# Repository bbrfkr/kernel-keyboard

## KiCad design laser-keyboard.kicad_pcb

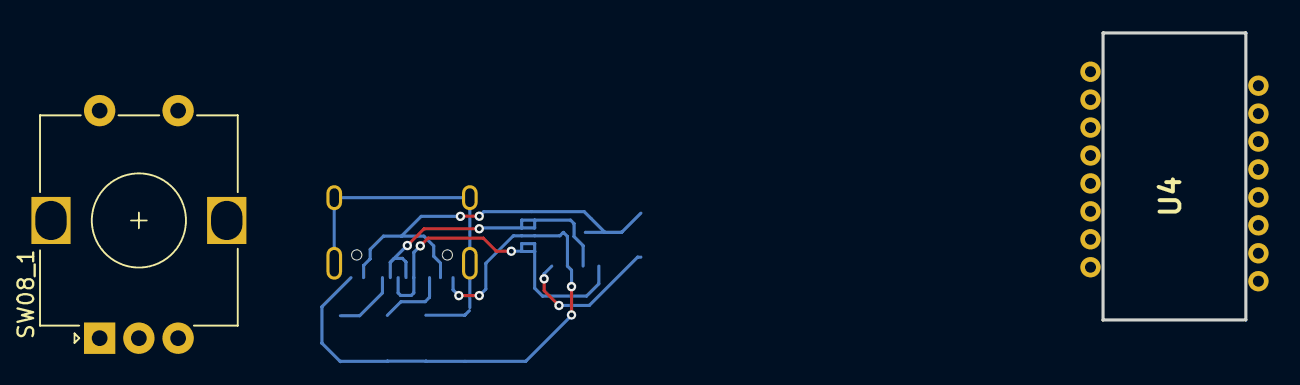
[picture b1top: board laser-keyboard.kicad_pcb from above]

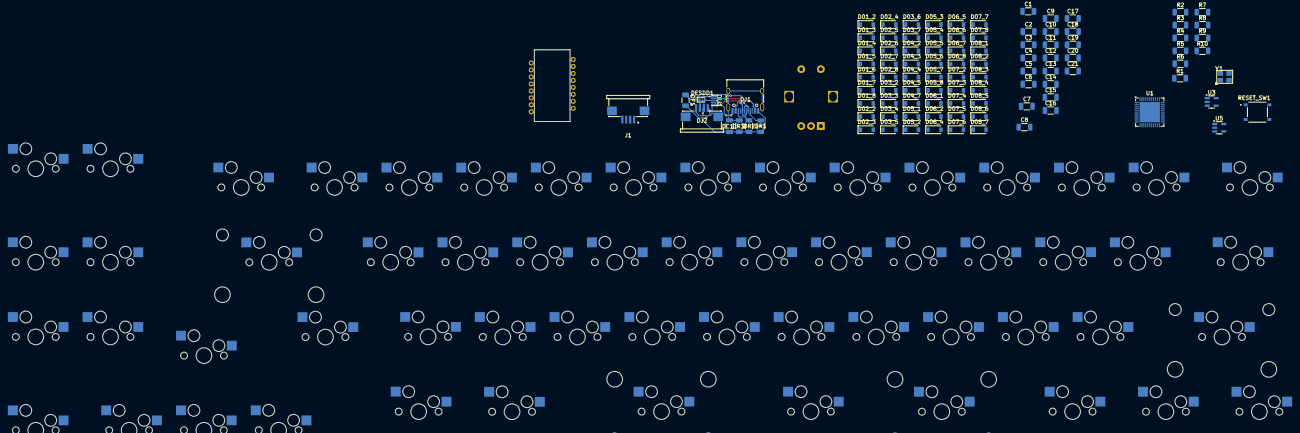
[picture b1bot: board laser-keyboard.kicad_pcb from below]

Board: 2 copper layers, 155 parts (100 on the bottom side), 103 nets.

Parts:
C1, C2: 22pF; C_1206_3216Metric
C3, C9, C13: 1μF; C_1206_3216Metric
C4, C5, C6, C8, C10, C12, C14, C17, C18, C19: 0.1μF; C_1206_3216Metric
C7, C11, C15, C20, C21: 10μF; C_1206_3216Metric
C16: 4.7μF; C_1206_3216Metric
D01_2, D01_3, D01_4, D01_5, D01_6, D01_7, D01_8, D02_2, D02_3, D02_4, D02_5, D02_6, D02_7, D02_8, D03_2, D03_3, D03_4, D03_5, D03_6, D03_7, D04_2, D04_3, D04_4, D04_5, D04_7, D05_1, D05_2, D05_3, D05_4, D05_5, D05_6, D05_7, D05_8, D06_1, D06_2, D06_4, D06_5, D06_6, D06_7, D06_8, D07_2, D07_3, D07_4, D07_5, D07_6, D07_7, D07_8, D08_1, D08_2, D08_3, D08_4, D08_5, D08_6, D08_7: D; D_SOD-123-Pretty
DC1: 4.7μF; C_1206_3216Metric
DESDD1: ESD5Z5V0; D_SOD-523
DF1: SMD0805-050-16V; Fuse_1206_3216Metric
DJ1: USB_C_Receptacle_USB2.0_16P; USB_C_Receptacle_HRO_TYPE-C-31-M-12
DJ2: Conn_01x04_Pin; FPC-SMD_4P-P1.00_1157-04AU
DR1, DR2: 5.1k; R_1206_3216Metric
DR3: 1M; R_1206_3216Metric
DU1: TPD4E05U06DQAR; USON-10_L2.5-W1.0-P0.50-BL
J1: Conn_01x04_Pin; FPC-SMD_4P-P1.00_1157-04AU
R1, R2: 22; R_1206_3216Metric
R3, R4, R9: 10k; R_1206_3216Metric
R5: 37.4k; R_1206_3216Metric
R6: 63.4K; R_1206_3216Metric
R7: 52.3k; R_1206_3216Metric
R8: 30.1k; R_1206_3216Metric
R10: 39; R_1206_3216Metric
RESET_SW1: TS-1187A-B-A-B; SW_TS-1187A-B-A-B
SW01_2, SW05_2: SW_Push; MXOnly-1.5U-Hotswap
SW01_3, SW01_4, SW01_5, SW01_6, SW01_7, SW01_8, SW02_3, SW02_4, SW02_5, SW02_6, SW02_7, SW02_8, SW03_3, SW03_4, SW03_5, SW03_6, SW03_7, SW05_1, SW05_3, SW05_4, SW05_5, SW05_6, SW05_7, SW05_8, SW06_1, SW06_4, SW06_5, SW06_6, SW06_7, SW06_8, SW07_2, SW07_4, SW07_5, SW07_6, SW07_7, SW07_8, SW08_2, SW08_3, SW08_4: SW_Push; MXOnly-1U-Hotswap
SW02_2, SW07_3: SW_Push; MXOnly-1.75U-Hotswap
SW03_2, SW06_2: SW_Push; MXOnly-2.25U-Hotswap
SW04_2, SW04_3, SW04_4, SW04_7, SW08_5, SW08_6: SW_Push; MXOnly-1.25U-Hotswap
SW04_5: SW_Push; MXOnly-2.25U-Hotswap-ReversedStabilizers
SW08_1: EncSW; RotaryEncoder_Alps_EC12E-Switch_Vertical_H20mm
SW08_7: SW_Push; MXOnly-2.75U-Hotswap-ReversedStabilizers
U1: ATmega32U4-M; QFN-44-1EP_7x7mm_P0.5mm_EP5.2x5.2mm
U3, U5: TPS73601DBV; SOT-23-5
U4: PMW3360DM-T2QU; PMW3360
Y1: 16Mhz; OSC-SMD_4P-L3.2-W2.5-BL

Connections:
+5V: C4.1, C5.1, C6.1, C7.1, C8.1, C9.1, C12.1, C13.1, J1.1, R4.1, U1.2 (UVCC), U1.7 (VBUS), U1.14 (VCC), U1.24 (AVCC), U1.34 (VCC), U1.44 (AVCC), U3.1 (IN), U3.3 (EN), U5.1 (IN), U5.3 (EN)
D+: J1.4, R1.2
D+5V: DF1.2, DJ2.4
D-: J1.3, R2.2
DD+: DJ1.A6 (D+), DJ1.B6 (D+), DJ2.1, DU1.4 (D2+), DU1.5 (D2-), DU1.6 (NC), DU1.7 (NC)
DD-: DJ1.A7 (D-), DJ1.B7 (D-), DJ2.2, DU1.1 (D1+), DU1.2 (D1-), DU1.9 (NC), DU1.10 (NC)
DGND: DC1.1, DESDD1.2 (A2), DJ1.A1 (GND), DJ1.A12 (GND), DJ1.B1 (GND), DJ1.B12 (GND), DJ2.3, DR1.1, DR2.1, DR3.1, DU1.3 (GND), DU1.8 (GND)
DGNDPWR: DC1.2, DJ1.S1 (SHIELD), DR3.2
DVCC: DESDD1.1 (A1), DF1.1, DJ1.A4 (VBUS), DJ1.A9 (VBUS), DJ1.B4 (VBUS), DJ1.B9 (VBUS)
GND: C1.1, C2.2, C3.2, C4.2, C5.2, C6.2, C7.2, C8.2, C9.2, C11.2, C12.2, C13.2, C15.2, C16.2, C17.2, C18.2, C19.2, C20.2, C21.2, J1.2, R3.1, R6.2, R8.2, RESET_SW1.C, RESET_SW1.D, SW08_1.C, U1.5 (UGND), U1.15 (GND), U1.23 (GND), U1.35 (GND), U1.43 (GND), U1.45 (GND), U3.2 (GND), U4.8 (GND), U5.2 (GND), Y1.2, Y1.4
MISO: U1.11 (PB3), U4.12 (MISO)
MOSI: U1.10 (PB2), U4.11 (MOSI)
MOTION: U1.12 (PB7), U4.9 (MOTION)
NCS: U1.8 (PB0), U4.13 (NCS)
unnamed: D01_2.2 (A), SW01_2.2
unnamed: D01_3.2 (A), SW01_3.2
unnamed: D01_4.2 (A), SW01_4.2
unnamed: D01_5.2 (A), SW01_5.2
unnamed: D01_6.2 (A), SW01_6.2
unnamed: D01_7.2 (A), SW01_7.2
unnamed: D01_8.2 (A), SW01_8.2
unnamed: D02_2.2 (A), SW02_2.2
unnamed: D02_3.2 (A), SW02_3.2
unnamed: D02_4.2 (A), SW02_4.2
unnamed: D02_5.2 (A), SW02_5.2
unnamed: D02_6.2 (A), SW02_6.2
unnamed: D02_7.2 (A), SW02_7.2
unnamed: D02_8.2 (A), SW02_8.2
unnamed: D03_2.2 (A), SW03_2.2
unnamed: D03_3.2 (A), SW03_3.2
unnamed: D03_4.2 (A), SW03_4.2
unnamed: D03_5.2 (A), SW03_5.2
unnamed: D03_6.2 (A), SW03_6.2
unnamed: D03_7.2 (A), SW03_7.2
unnamed: D04_2.2 (A), SW04_2.2
unnamed: D04_3.2 (A), SW04_3.2
unnamed: D04_4.2 (A), SW04_4.2
unnamed: D04_5.2 (A), SW04_5.2
unnamed: D04_7.2 (A), SW04_7.2
unnamed: D05_1.2 (A), SW05_1.2
unnamed: D05_2.2 (A), SW05_2.2
unnamed: D05_3.2 (A), SW05_3.2
unnamed: D05_4.2 (A), SW05_4.2
unnamed: D05_5.2 (A), SW05_5.2
unnamed: D05_6.2 (A), SW05_6.2
unnamed: D05_7.2 (A), SW05_7.2
unnamed: D05_8.2 (A), SW05_8.2
unnamed: D06_1.2 (A), SW06_1.2
unnamed: D06_2.2 (A), SW06_2.2
unnamed: D06_4.2 (A), SW06_4.2
unnamed: D06_5.2 (A), SW06_5.2
unnamed: D06_6.2 (A), SW06_6.2
unnamed: D06_7.2 (A), SW06_7.2
unnamed: D06_8.2 (A), SW06_8.2
unnamed: D07_2.2 (A), SW07_2.2
unnamed: D07_3.2 (A), SW07_3.2
unnamed: D07_4.2 (A), SW07_4.2
unnamed: D07_5.2 (A), SW07_5.2
unnamed: D07_6.2 (A), SW07_6.2
unnamed: D07_7.2 (A), SW07_7.2
unnamed: D07_8.2 (A), SW07_8.2
unnamed: D08_1.2 (A), SW08_1.S1
unnamed: D08_2.2 (A), SW08_2.2
unnamed: D08_3.2 (A), SW08_3.2
unnamed: D08_4.2 (A), SW08_4.2
unnamed: D08_5.2 (A), SW08_5.2
unnamed: D08_6.2 (A), SW08_6.2
unnamed: D08_7.2 (A), SW08_7.2
unnamed: DJ1.A5 (CC1), DR1.2
unnamed: DJ1.B5 (CC2), DR2.2
unnamed: R1.1, U1.4 (D+)
unnamed: R2.1, U1.3 (D-)
unnamed: C3.1, U1.6 (UCAP)
unnamed: C1.2, U1.17 (XTAL1), Y1.3
unnamed: C2.1, U1.16 (XTAL2), Y1.1
unnamed: R3.2, U1.33 (~HWB/PE2)
unnamed: C10.2, R5.2, R6.1, U3.4 (FB)
unnamed: R10.2, U4.15 (LED_P)
unnamed: R9.1, U4.7 (NRESET)
unnamed: C16.1, C19.1, U4.3 (VDDPIX)
unnamed: C14.2, R7.2, R8.1, U5.4 (FB)
RESET: R4.2, RESET_SW1.A, RESET_SW1.B, U1.13 (~RESET)
RE_A: SW08_1.A, U1.41 (PF0)
RE_B: SW08_1.B, U1.40 (PF1)
SCLK: U1.9 (PB1), U4.10 (SCLK)
VDD_3_3v: C14.1, C15.1, C18.1, C21.1, R7.1, R9.2, U4.5 (VDDIO), U5.5 (OUT)
VDD_SS: C10.1, C11.1, C17.1, C20.1, R5.1, R10.1, U3.5 (OUT), U4.4 (VDD)
col01: SW05_1.1, SW06_1.1, SW08_1.S2, U1.31 (PC6)
col02: SW01_2.1, SW02_2.1, SW03_2.1, SW04_2.1, SW05_2.1, SW06_2.1, SW07_2.1, SW08_2.1, U1.32 (PC7)
col03: SW01_3.1, SW02_3.1, SW03_3.1, SW04_3.1, SW05_3.1, SW07_3.1, SW08_3.1, U1.18 (PD0)
col04: SW01_4.1, SW02_4.1, SW03_4.1, SW04_4.1, SW05_4.1, SW06_4.1, SW07_4.1, SW08_4.1, U1.19 (PD1)
col05: SW01_5.1, SW02_5.1, SW03_5.1, SW04_5.1, SW05_5.1, SW06_5.1, SW07_5.1, SW08_5.1, U1.20 (PD2)
col06: SW01_6.1, SW02_6.1, SW03_6.1, SW05_6.1, SW06_6.1, SW07_6.1, SW08_6.1, U1.21 (PD3)
col07: SW01_7.1, SW02_7.1, SW03_7.1, SW04_7.1, SW05_7.1, SW06_7.1, SW07_7.1, SW08_7.1, U1.25 (PD4)
col08: SW01_8.1, SW02_8.1, SW05_8.1, SW06_8.1, SW07_8.1, U1.22 (PD5)
row01: D01_2.1 (K), D01_3.1 (K), D01_4.1 (K), D01_5.1 (K), D01_6.1 (K), D01_7.1 (K), D01_8.1 (K), U1.26 (PD6)
row02: D02_2.1 (K), D02_3.1 (K), D02_4.1 (K), D02_5.1 (K), D02_6.1 (K), D02_7.1 (K), D02_8.1 (K), U1.27 (PD7)
row03: D03_2.1 (K), D03_3.1 (K), D03_4.1 (K), D03_5.1 (K), D03_6.1 (K), D03_7.1 (K), U1.39 (PF4)
row04: D04_2.1 (K), D04_3.1 (K), D04_4.1 (K), D04_5.1 (K), D04_7.1 (K), U1.38 (PF5)
row05: D05_1.1 (K), D05_2.1 (K), D05_3.1 (K), D05_4.1 (K), D05_5.1 (K), D05_6.1 (K), D05_7.1 (K), D05_8.1 (K), U1.37 (PF6)
row06: D06_1.1 (K), D06_2.1 (K), D06_4.1 (K), D06_5.1 (K), D06_6.1 (K), D06_7.1 (K), D06_8.1 (K), U1.36 (PF7)
row07: D07_2.1 (K), D07_3.1 (K), D07_4.1 (K), D07_5.1 (K), D07_6.1 (K), D07_7.1 (K), D07_8.1 (K), U1.29 (PB5)
row08: D08_1.1 (K), D08_2.1 (K), D08_3.1 (K), D08_4.1 (K), D08_5.1 (K), D08_6.1 (K), D08_7.1 (K), U1.28 (PB4)

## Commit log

2024-11-02 initial
